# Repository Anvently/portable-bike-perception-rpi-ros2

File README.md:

# Cyclo-safe : a multi-sensor bike perception module (Camera, Dual 360° Lidar, GPS, Raspberry Pi, ROS2)

> The aim of the CycloSafe project is to improve cyclist safety by rigorously quantifying the risks they face, with a particular focus on those occurring when being overtaken by a motor vehicle.
> 
> To do this, we have equipped a bicycle with LIDARs (Light Detection and Ranging), a camera and a GNSS antenna.

This repository contains :
- the firmware intended to run on a **Raspberry Pi** to operate all the sensors and **take measurements**
- Various tools to **export**, **visualize**, and **analyze** the collected data
- Files required for **3D printing the case**
- File needed to manufacture the **dedicated PCB**.  
It was developed as part of an experimental data acquisition system for an academic research study on cyclist safety.

https://github.com/user-attachments/assets/d5b68dda-f3fe-4f50-86e3-c243446fb8e7

## Structure

> [**core/**](core/README.md): Directory intended to be installed on the Raspberry Pi. Contains:
> 	- ROS installation script
> 	- CycloSafe environment setup script
> 	- systemd services setup script
> 	- source code for the different ROS nodes

> [**design/**](design/README.md): Contains files related to the machining of the case and the dedicated PCB.

> [**scripts/**](scripts/README.md): Contains scripts useful for retrieving and exporting data.

> [**viewer/**](viewer/README.md): Directory intended to be installed on the host machine. Contains a set of tools for visualizing and analyzing the data.
> - [**ROS2.md**](viewer/ROS2.md): Documentation related to ROS2 and its use in the project.

> [**network.md**](network.md): Instructions for network configuration on both the host and the Raspberry Pi, enabling interaction between the two machines.

## About the Cyclo-safe project

This project is part of the broader **CycloSafe** research initiative conducted at the **Institut national de l’information géographique et forestière (IGN)**, which aims **to quantify the risks faced by cyclists when being overtaken by motor vehicles**.

This repository is dedicated **exclusively to the design and implementation of the acquisition module** used to collect measurement data for the study, along with a set of **tools for processing, visualizing, and analyzing** the recorded data.

It does **not** present or discuss the **results** of the study itself, and should not be directly associated with its conclusions or interpretations.

For more information on the full **CycloSafe** study, see:  
Emmanuel Cledat, Dirk Lauinger, Aymeric Dutremble, Maeve Blarel, Damien Louis Peller, Tristan Geslain, Alexandre Esteoulle, Elisabeth Giroux, Gabin Bourlon, Nicolas Pirard, Eric Ta — ***Cyclo-Safe: Quantitative study of the risks to which cyclists are exposed during their daily commute***.

## License

This project is licensed under the **CeCILL-B v1** license, a free software license fully compliant with French law, **based on the BSD 2-Clause license** and the principles of open source.

**Scope of the license** — The following materials are covered by the CeCILL-B license:
- Firmware code based on ROS2
- All project installation scripts and data analysis scripts
- Source code of data analysis tools, based on Qt and ROS2
- PCB design files
- 3D models and any corresponding f3d source files
- Assembly and user manuals for the module

You are **free to**:
- Use, modify, and redistribute this project under the terms of the CeCILL-B license
- Use this project for both **academic** and **commercial** purposes, without the strong copyleft constraints of GPL-like licenses
- Incorporate this code into proprietary software, as long as you respect the attribution requirements

You must:
- Include a copy of the CeCILL-B license with any redistributed version
- Retain notices of authorship and copyright
- Clearly indicate any modifications made

Author: [Nicolas Pirard (@Anvently)](https://github.com/Anvently)  
Contact: [pirard.nicolas@hotmail.fr](mailto:pirard.nicolas@hotmail.fr)  
Additional contributors: See [CONTRIBUTORS.md](./CONTRIBUTORS.md)

📄 Full license text: [CeCILL-B v1](http://www.cecill.info/licences/Licence_CeCILL-B_V1-en.html)  

📄 French version: [CeCILL-B v1](https://cecill.info/licences/Licence_CeCILL-B_V1-fr.html)  

---

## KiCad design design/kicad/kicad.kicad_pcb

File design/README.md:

# Cyclosafe design

Ce dossier contient les fichiers relatifs à la fabrication du boitier destiné à recevoir tous les composants ainsi que les fichiers de fabrication du PCB dédié.

- [Cyclosafe design](#cyclosafe-design)
- [Liste du matériel (BOM)](#liste-du-matériel-bom)
	- [COMPOSANTS](#composants)
	- [Quincaillerie](#quincaillerie)
	- [Inserts](#inserts)
	- [Total](#total)
- [Electronique](#electronique)
	- [Montage complet](#montage-complet)
	- [PCB dédié](#pcb-dédié)
		- [Fonctions](#fonctions)
		- [Schéma](#schéma)
		- [Aperçu](#aperçu)
- [Boitier imprimé en 3D](#boitier-imprimé-en-3d)
	- [Module waveshare UPS hat](#module-waveshare-ups-hat)
		- [Spécifications](#spécifications)
		- [Aperçu](#aperçu-1)
- [Fixation au vélo](#fixation-au-vélo)
- [Module de mesure amovible](#module-de-mesure-amovible)
	- [Partie haute](#partie-haute)
	- [Partie basse](#partie-basse)

---

https://github.com/user-attachments/assets/05b4201d-2b15-44bb-a8c5-ab20a0cb3d47

# Liste du matériel (BOM)

## COMPOSANTS

| Quantité | Nom de la pièce | Fonction | Masse (g) | Type | Origine | Coût estimé |
|----------|-----------------|----------|-----------|------|---------|-------------|
| 1 | Raspberry Pi 4 Model B | Firmware | 75.00 | PCB | Achat | 65.00 |
| 1 | UPS-HAT | Batterie | 120.00 | PCB | Achat | 22.00 |
| 1 | PCB custom | Électronique | 30.00 | PCB | Fabrication par un tiers | 8.75 |
| 1 | Raspberry Pi HQ Camera M12 mount | Capteur | 30.40 | Capteur | Achat | 52.00 |
| 1 | Objectif grand angle M12 | Capteur | 100 | Accessoire | Achat | 25.00 |
| 2 | Slamtec RPLiDAR C1 | Capteur | 110.00 | Capteur | Achat | 84.00 |
| 1 | Assemblage F | Fixation | 90.00 | Structure | Impression | 2.00 |
| 1 | Collier | Fixation | 37.00 | Structure | Impression | 0.5 |
| 1 | L76x GPS Module | Capteur | 5.00 | PCB | Achat | 15.00 |
| 1 | Boîtier bas | Structure | 130.00 | Structure | Impression | 1.89 |
| 1 | Boîtier haut | Structure | 101.00 | Structure | Impression | 2.23 |
| 1 | Carte SD | Firmware | 2.00 | Accessoire | Achat | 25.00 |
| 2 | Accu 18650 - 3400mAh | Batterie | 46.00 | Accessoire | Achat | 18.50 |
| 1 | Couvercle carte SD | Structure | 3.30 | Structure | Impression | 0.07 |
| 1 | Ficelle pour pin de verrouillage (diamètre < 2mm) | Fixation | 1.00 | Accessoire | Achat | 0.05 |
| 1 | Pin de verrouillage | Fixation | 1.65 | Structure | Impression | 0.05 |
| 1 | Câble molex picoblade 510210800 8-pin double-M 20cm | Connection gps-pcb | 2.00 | Accessoire | Achat | 0.50 |

## Quincaillerie

| Quantité | Nom de la pièce | Fonction | Masse (g) | Type | Origine | Coût estimé |
|----------|-----------------|----------|-----------|------|---------|--|
| 1 | Vis à tête hexagonale M2.5x6 | Trappe carte SD | 0.487 | Quincaillerie | Achat | 0.05
| 4 | Entretoise M/F M2.5x12 | Entretoise Raspberry | 1.999 | Quincaillerie | Achat | 0.50
| 4 | Entretoise M/F M2.5x18 | Entretoise HAT | 2.393 | Quincaillerie | Achat | 0.50
| 8 | Vis à tête hexagonale M2.5x12 | Lidars | 0.702 | Quincaillerie | Achat | 0.05
| 2 | Vis à tête hexagonale M2x8 | GPS | 0.341 | Quincaillerie | Achat | 0.05
| 3 | Vis à tête hexagonale M3x6 | Boîtiers | 0.796 | Quincaillerie | Achat | 0.05
| 8 | Vis à tête hexagonale M2.5x10 | UPS HAT & caméra | 0.630 | Quincaillerie | Achat | 0.05
| 1 | Vis à tête hexagonale M3x0.5x40 | Axe centrale du pin de blocage | 2.569 | Quincaillerie | Achat | 0.10
| 2 | Vis à tête hexagonale M4x0.7x40 | Collier | 4.776 | Quincaillerie | Achat | 0.10

## Inserts

| Quantité | Nom de la pièce | Fonction | Masse (g) | Type | Origine | Coût estimé
|----------|-----------------|----------|-----------|------|---------|--|
| 2 | Insert M4x8x6 | Collier | 2.00 | Quincaillerie | Achat | 0.08
| 1 | Insert M3x4x4.5 | Emboîtement supérieur | 1.00 | Quincaillerie | Achat | 0.05
| 2 | Insert M3x3x4.5 | Emboîtement latéral | 1.00 | Quincaillerie | Achat | 0.04
| 4 | Insert M2.5x4x3.5 | Raspberry | 1.00 | Quincaillerie | Achat | 0.04
| 2 | Insert M2x5x3.5 | GPS | 1.00 | Quincaillerie | Achat | 0.04
| 5 | Insert M2.5x5x3.5 | Couvercle SD + caméra | 1.00 | Quincaillerie | Achat | 0.04

## Total

| Quantité | Nom de la pièce | Fonction | Masse (g) | Type | Origine |Coût estimé
|----------|-----------------|----------|-----------|------|---------|--|
|Poids|||1102.25||
|Coût||||||431.17€

# Electronique

Le coeur du boitier comporte un assemblage de 3 circuits imprimés emboités les uns par desus les autres :
- un rapbeerry Pi 4B sur lequel vient se brancher la caméra
- un PCB personnalisé sur lequel vient se brancher les capteurs (2 LiDARS + un module GNSS)
- un module UPS (*Uninterruptible Power Supply*) alimentés par deux accus 18650 permettant de fournir le courant nécessaire (jusqu'à 3A), de protéger le circuit et de gérer la recharge

## Montage complet

## PCB dédié

 ### Fonctions
- permet de connecter les capteurs aux différentes interfaces UARTs du raspberry :
  - UART1 : LiDAR 1 (supérieur)
  - UART2 : LiDAR 2 (arrière)
  - UART5 : module GNSS
- intègre 3 LEDs pour avertir l'utilisateur des situations suivantes :
  - batterie faible (< 20 %) : voyant rouge allumé
  - carte sd pleine : voyant bleu allumé
  - démarrage/arrêt en cours : voyant jaune allumé sans clignotement
  - mesure en cours : voyant jaune clignotant
- intègre un bouton poussoir permettant de déclencher l'arrêt des mesures et d'éteindre en douceur le raspberry

### Schéma

### Aperçu

# Boitier imprimé en 3D

Le dossier [`kicad/`](kicad/) contient le projet Kicad 9.0 d'un PCB sur lequel viennent se brancher les différents capteurs et composants actifs (LEDs et bouton d'extinction).

Il prend la forme d'un hat pour raspberry et se connecte via le header de 40 pins.

## Module waveshare UPS hat

Il s'agit d'une alimentation non interruptible commercialisée par Waveshare.

### Spécifications

- alimenté par 2 accus 18650
- permet une utilisation constante du raspberry via batterie ou pendant la recharge sur secteur
- protection contre les court-circuits, polarité inversée, surcharge/décharge des batterie
- jusqu'à 2.5A en 5V
- monitoring de la tension des batteries (permettant de calculer le pourcentage restant) et de la consommation instantanée

### Aperçu

# Fixation au vélo

Cette partie là demeure sur la tige selle.

Un collier facilement déformable est placé autour de la tige selle et vient verrouiller l'assemblage femelle avec deux vis M4.

Le design du  collier est basé sur  par [**<ins>un modèle réalisé par Metamere</ins>**](https://www.printables.com/model/125810-bens-better-dropper-post-seat-bag-adapters-264-22-)  trouvé sur *printables.com* et distribué sous licence Creative Commons.

Il a été allongé, épaissi et simplifié par rapport au modèle original.

Le sytème de fixation est inspiré de celui du projet Open Source [**<ins>Open bike sensor</ins>**](https://github.com/openbikesensor/OpenBikeSensor3dPrintableCase), en particulier le système de glissière entre le support fixe demeurant sur la tige selle et le boitier principal.

# Module de mesure amovible

Il vient se glisseer dans l'assemblage femelle fixé sur la tige selle.

Le pin de verrouillage de la fixation s'insère dans un des trous prévus à cet effet et peut tourner sur lui-même afin de maintenir l'assemblage en place (un de chaque côté selon la place disponible sous ou au dessus du boitier).

Il se compose d'une partie basse et d'une partie haute qui viennent se clipser ensemble. 3 vis M3 permettent de verrouiller l'assemblage des deux boitiers.

## Partie haute

## Partie basse

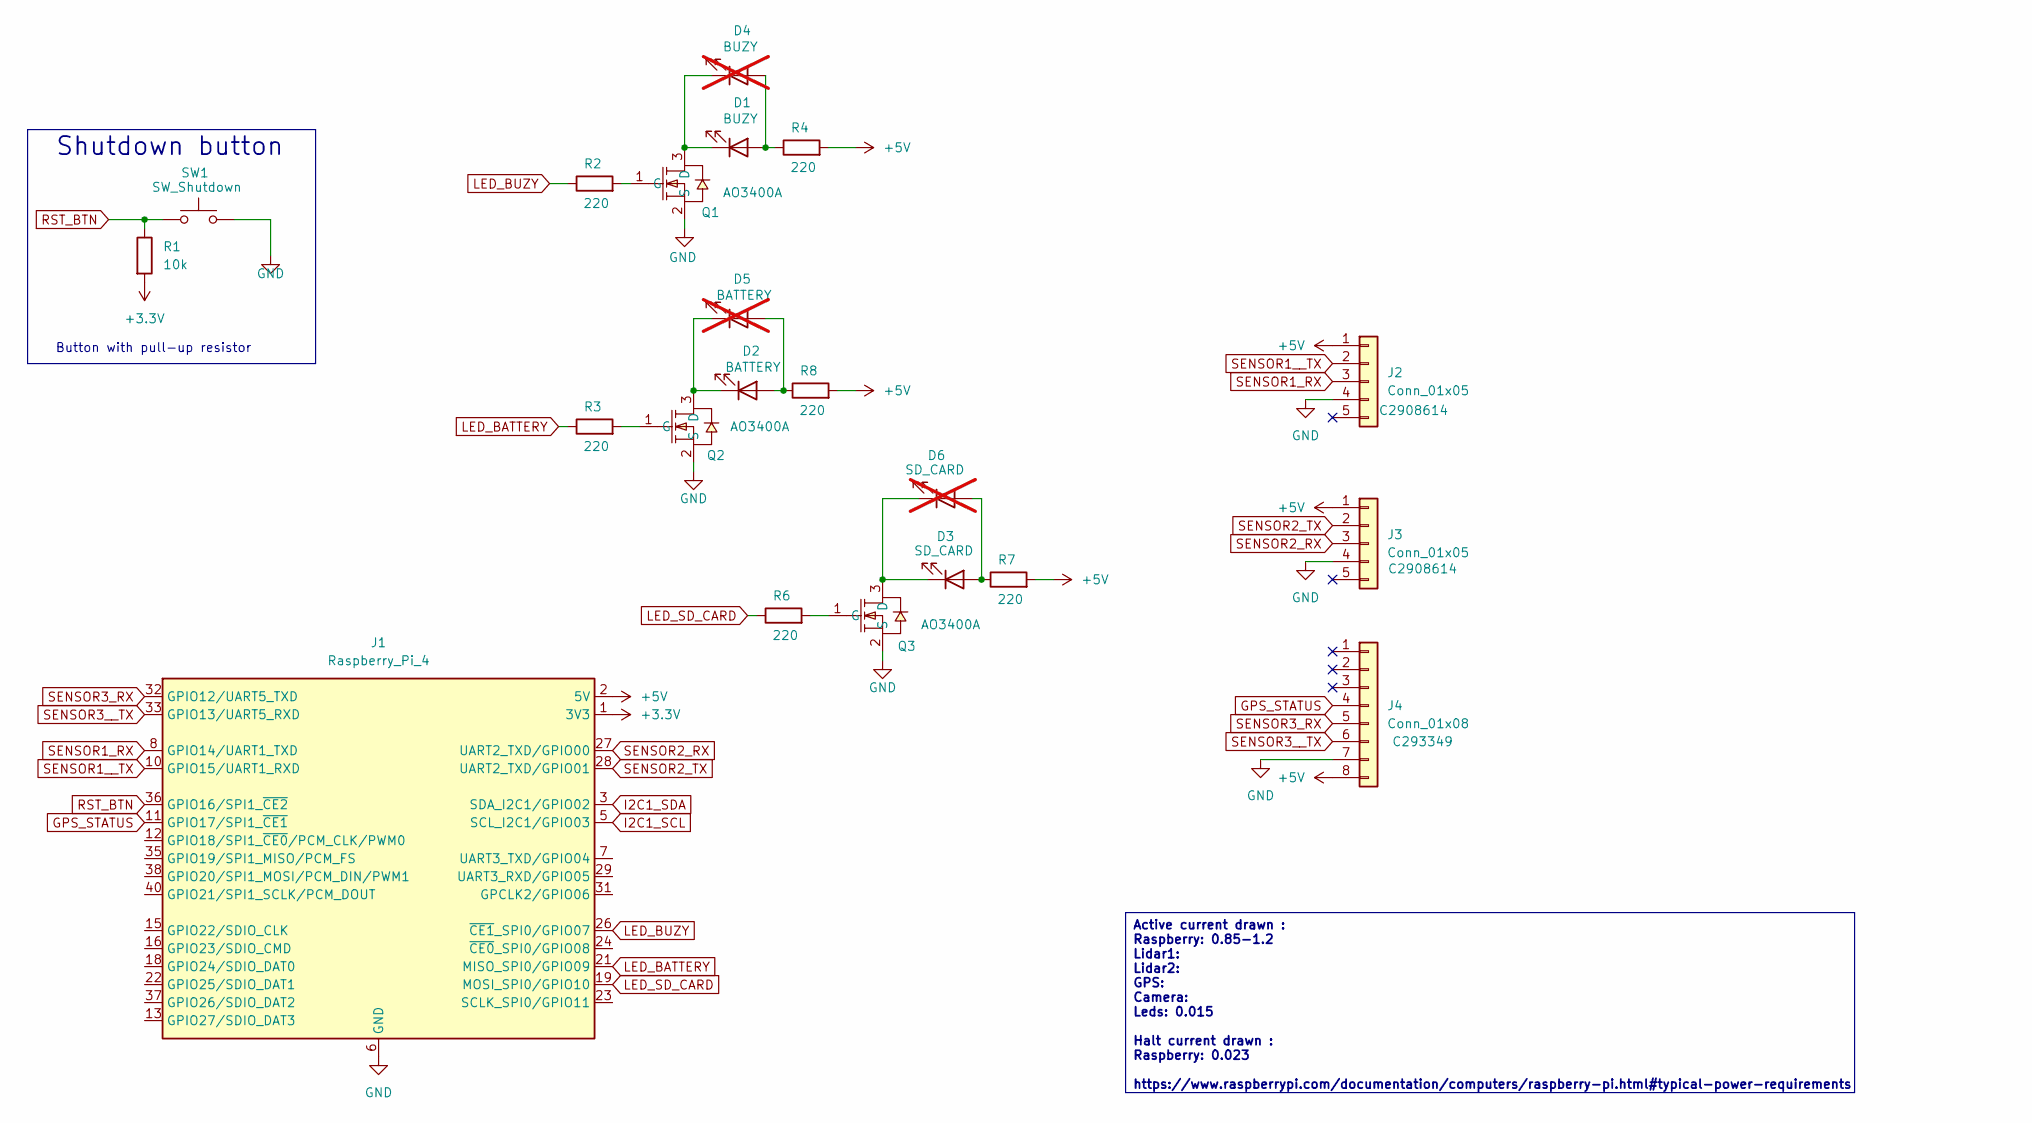
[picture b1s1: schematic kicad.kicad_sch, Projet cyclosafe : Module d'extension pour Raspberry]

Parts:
D1: BUZY; LED-SMD_L1.7-W0.6-RD-custom; LCSC Part C133119
D2: BATTERY; LED-SMD_L1.7-W0.6-RD-custom; LCSC Part C125114
D3: SD_CARD; LED-SMD_L1.7-W0.6-RD-custom; LCSC Part C125115
D4: BUZY; LED-TH_BD3.9-P2.54-FD; LCSC Part C133119; not fitted
D5: BATTERY; LED-TH_BD3.9-P2.54-FD; LCSC Part C125114; not fitted
D6: SD_CARD; LED-TH_BD3.9-P2.54-FD; LCSC Part C125115; not fitted
J1: Raspberry_Pi_4; HDR-TH_40P-P2.54-V-F-R2-C20-S2.54-2-reveresed; LCSC Part C35165
J2, J3: Conn_01x05; CONN-TH_WAFER-HA254WZ-5A; LCSC Part C2908614
J4: Conn_01x08; Molex_PicoBlade_53261-0871_1x08-1MP_P1.25mm_Horizontal; LCSC Part C293349
Q1, Q2, Q3: AO3400A; SOT-23-3_L2.9-W1.3-P1.90-LS2.4-BR; LCSC Part C20917
R1: 10k; R_0805_2012Metric; LCSC Part C17414
R2, R3, R4, R6, R7, R8: 220; R_0805_2012Metric; LCSC Part C17557
SW1: SW_Shutdown; SW-TH_TK-6580B-2; LCSC Part C2689830

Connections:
+3.3V: J1.1 (3V3), J1.17 (3V3), R1.2
+5V: J1.2 (5V), J1.4 (5V), J2.1, J3.1, J4.8, R4.2, R7.2, R8.2
GND: J1.6 (GND), J1.9 (GND), J1.14 (GND), J1.20 (GND), J1.25 (GND), J1.30 (GND), J1.34 (GND), J1.39 (GND), J2.4, J3.4, J4.7, Q1.2 (S), Q2.2 (S), Q3.2 (S), SW1.2
GPS_STATUS: J1.11 (GPIO17/SPI1_~CE1), J4.4
I2C1_SCL: J1.5 (SCL_I2C1/GPIO03)
I2C1_SDA: J1.3 (SDA_I2C1/GPIO02)
LED_BATTERY: J1.21 (MISO_SPI0/GPIO09), R3.1
LED_BUZY: J1.26 (~CE1_SPI0/GPIO07), R2.1
LED_SD_CARD: J1.19 (MOSI_SPI0/GPIO10), R6.1
unnamed: D1.2 (A), D4.2 (A), R4.1
unnamed: D1.1 (K), D4.1 (K), Q1.3 (D)
unnamed: D2.2 (A), D5.2 (A), R8.1
unnamed: D2.1 (K), D5.1 (K), Q2.3 (D)
unnamed: D3.2 (A), D6.2 (A), R7.1
unnamed: D3.1 (K), D6.1 (K), Q3.3 (D)
unnamed: Q1.1 (G), R2.2
unnamed: Q2.1 (G), R3.2
unnamed: Q3.1 (G), R6.2
RST_BTN: J1.36 (GPIO16/SPI1_~CE2), R1.1, SW1.1
SENSOR1_RX: J1.8 (GPIO14/UART1_TXD), J2.3
SENSOR1__TX: J1.10 (GPIO15/UART1_RXD), J2.2
SENSOR2_RX: J1.27 (UART2_TXD/GPIO00), J3.3
SENSOR2_TX: J1.28 (UART2_TXD/GPIO01), J3.2
SENSOR3_RX: J1.32 (GPIO12/UART5_TXD), J4.5
SENSOR3__TX: J1.33 (GPIO13/UART5_RXD), J4.6

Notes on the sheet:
Button with pull-up resistor
Shutdown button
Active current drawn : Raspberry: 0.85-1.2 Lidar1: Lidar2: GPS: Camera: Leds: 0.015 Halt current drawn : Raspberry: 0.023 https://www.raspberrypi.com/documentation/computers/raspberry-pi.html#typical-power-requirements

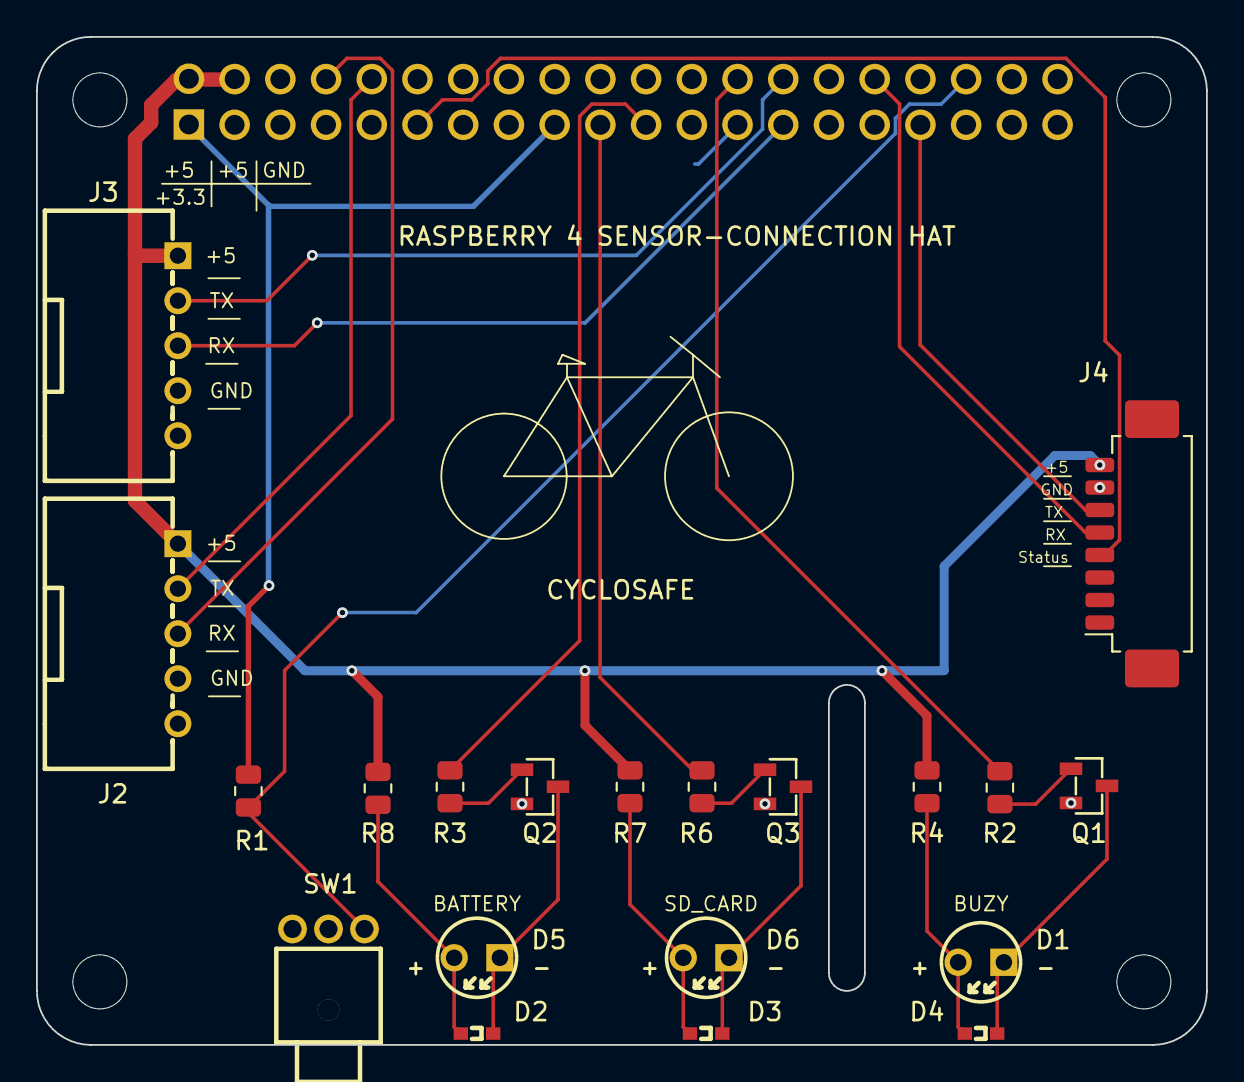
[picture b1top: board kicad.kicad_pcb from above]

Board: 2 copper layers, 65.0 x 56.0 mm, 21 parts (1 on the bottom side), 23 nets.

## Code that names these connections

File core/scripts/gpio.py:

#!/usr/bin/env python3
# -*- coding: utf-8 -*-
# Crerated on Tue Aug 05 2025
# Updated on Tue Aug 05 2025
#
# This file is part of Cyclosafe
# Copyright (c) 2025 Nicolas Pirard @Anvently
#
# This software is governed by the CeCILL license under French law and
# abiding by the rules of distribution of free software. You can use,
# modify and/or redistribute the software under the terms of the CeCILL
# license as circulated by CEA, CNRS and INRIA at:
# https://cecill.info/licences/Licence_CeCILL-B_V1-en.html

import os, time, sys, signal
import battery_monitor
import psutil
from battery_monitor import INA219
from gpiozero import Button, PWMLED

BTN_RST_GPIO = 16
LED_BATTERY_GPIO = 9
LED_BUZY_GPIO= 7
LED_SD_CARD_GPIO = 10

LED_BRIGHTNESS = float(os.getenv("LED_BRIGHTNESS", "1.0"))

button = Button(BTN_RST_GPIO, pull_up=True, bounce_time=0.1)

class BatteryException(Exception):
	pass

BUTTON_SHUTDOWN = 255
BATTERY_SHUTDOWN = 254

NBR_CELLS = 2
CHARGE_VOLTAGE = 4.2
MIN_VOLTAGE = 3

VOLTAGE_RANGE = CHARGE_VOLTAGE - MIN_VOLTAGE
BUS_CHARGE_VOLTAGE = NBR_CELLS * CHARGE_VOLTAGE
BATTERY_VOLTAGE_TRESHOLD = BUS_CHARGE_VOLTAGE - (NBR_CELLS * VOLTAGE_RANGE)

LOW_BATTERY_PERCENT = float(os.getenv("LOW_BATTERY_PERCENT", "0.2"))
LOW_BATTERY_TRESHOLD = BATTERY_VOLTAGE_TRESHOLD + (LOW_BATTERY_PERCENT * NBR_CELLS * VOLTAGE_RANGE)

LOW_STORAGE_TRESHOLD = int(os.getenv("LOW_STORAGE_TRESHOLD", "512"))

class GPIOController():
	def __init__(self):
		GPIOController.colors = [(255,0,0), (0,255,0), (0,0,255), (255,255,0), (0,255,255), (255,255,255)]
		self.color_index = 0
		self.gpio_state = {LED_BATTERY_GPIO: False, LED_BUZY_GPIO: False, LED_SD_CARD_GPIO: False}
		
		self.led_battery = PWMLED(LED_BATTERY_GPIO)
		self.led_busy = PWMLED(LED_BUZY_GPIO)
		self.led_sd = PWMLED(LED_SD_CARD_GPIO)
		
		for gpio in self.gpio_state:
			self.turn_off(gpio)
		self.pos = 0
		self.enable = True

		self.ina219 = INA219(1, addr=0x42)

	def turn_on(self, gpio):
		led = self._get_led(gpio)
		if led:
			led.value = LED_BRIGHTNESS
		self.gpio_state[gpio] = True

	def turn_off(self, gpio):
		led = self._get_led(gpio)
		if led:
			led.off()
		self.gpio_state[gpio] = False

	def _get_led(self, gpio):
		if gpio == LED_BATTERY_GPIO:
			return self.led_battery
		elif gpio == LED_BUZY_GPIO:
			return self.led_busy
		elif gpio == LED_SD_CARD_GPIO:
			return self.led_sd
		return None

	def toggle(self, gpio):
		if self.gpio_state[gpio]:
			self.turn_off(gpio)
		else:
			self.turn_on(gpio)

	def check_battery_state(self):
		if not self.ina219:
			return
		try:
			bus_voltage = self.ina219.get_bus_voltage_V()
		except:
			return
		if bus_voltage < BATTERY_VOLTAGE_TRESHOLD:
			raise BatteryException()
		elif bus_voltage < LOW_BATTERY_TRESHOLD:
			self.turn_on(LED_BATTERY_GPIO)

	def cleanup(self):
		self.turn_off(LED_BATTERY_GPIO)
		self.turn_off(LED_SD_CARD_GPIO)
		self.turn_on(LED_BUZY_GPIO)
		self.led_battery.close()
		self.led_sd.close()

	def routine(self, blink = True):
		shutdown_type = 0
		try:
			count = 0
			while not button.is_pressed:
				if count % 40 == 0:
					self.check_battery_state()
				if count % 120 == 0:
					self.check_sd_card()
				if blink:
					self.toggle(LED_BUZY_GPIO)
				time.sleep(0.25)
				count += 1
			print("Shutting down...")
			shutdown_type = BUTTON_SHUTDOWN
		except BatteryException:
			shutdown_type = BATTERY_SHUTDOWN
		
		self.cleanup()
		return shutdown_type

	def check_sd_card(self) -> bool:
		mb_available = psutil.disk_usage("/").free / 1024 / 1024
		print(mb_available, LOW_STORAGE_TRESHOLD)
		if (mb_available < LOW_STORAGE_TRESHOLD):
			self.turn_on(LED_SD_CARD_GPIO)
			return False
		self.turn_off(LED_SD_CARD_GPIO)
		return True

gpio_controler = GPIOController()

def signal_handler(signum, frame):
	gpio_controler.cleanup()
	sys.exit(0)

def main(args=None):
	global gpio_controler
	
	signal.signal(signal.SIGINT, signal_handler)
	signal.signal(signal.SIGTERM, signal_handler)
	shutdown_code = 0
	try:
		if gpio_controler.check_sd_card() == False:
			shutdown_code = gpio_controler.routine(blink=False)
		else:
			shutdown_code = gpio_controler.routine(blink=True)
	except:
		pass

	sys.exit(shutdown_code)

if __name__ == '__main__':
	main()

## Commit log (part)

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2025-03-10 inital commit, working on dockerfile
2025-03-10 fixed dockerfile
2025-03-10 dockerifle
2025-03-12 rm extra files
2025-03-12 sensor node
2025-03-12 added launch file with parameterized sensor node
2025-03-12 aded camera node (not tested)
2025-03-12 added camera_cv node
2025-03-13 camera node working - need to implement image queue
2025-03-13 new structure
2025-03-13 added save_files service
2025-03-13 tested save_files service
2025-03-13 fixed executable name
2025-03-14 added abstract serial sensor node and updated sensor example, added gps publisher base code
2025-03-17 gpio node
2025-03-17 test with gpio ok
2025-03-17 color palette
2025-03-17 wheel
2025-03-17 fixed wheel
2025-03-17 shutdown script
2025-03-17 changed gpio, added shutdown system
2025-03-18 gps node implemented
2025-03-18 fix exception handler for parsing serial node
2025-03-19 added cpp lidar node
2025-03-20 cpp lidar node: serial class implemented, some issue with line parsing and non printable character
2025-03-20 fixed lidar cpp
2025-03-20 eod - working on aggregator node
2025-03-21 hub - almost at the same point that python node - ready to compile
2025-03-21 fixed compil errors
2025-03-21 issue with future handling
2025-03-21 hub node: separate hpp/cpp files
2025-03-24 implemented ttldeque + outfile + suscriber_handler - ready to test
2025-03-24 hub timestamps fixed and working. TODO: Need the camera node to use ms timestamp synchronized with the hub. Need something else (forgot)
2025-03-25 global time implemented and working. TODO: implement ros time in ASerialSensor
2025-03-26 launch config implemented: custom log_level/log folder/ all node share the same start_time and use ros time
2025-03-26 implemented ros bag in launch description
2025-03-26 fixing to cpp 17
2025-03-26 c++ 17 compiled
2025-03-26 now using compressed image msg
2025-03-26 fioxed
2025-03-26 added rp_lidar to launch config
2025-03-26 debugging picamera
2025-03-27 *range_circle*
2025-03-27 viewer launch configuration ok
2025-03-27 added scan file output
2025-03-27 changed gpio routine
2025-03-28 small fix
2025-03-28 enabled compression on launch
2025-03-28 added port name resolution + changed camera frquency
2025-03-28 fixed
2025-03-28 preview fixed
2025-03-28 optimize camera node
2025-03-28 fixed camera
2025-03-28 changed image view in view launch config
2025-03-28 added doubloon directory security, but will never happen
2025-04-01 implementing gps interface and improving gps informations
2025-04-03 4 sonar config + rplidar on uart
2025-04-03 tag update sonar
2025-04-03 removed camera preview
2025-04-03 camera adjust
2025-04-04 updated sonar visualizations
2025-04-04 gpio node now systemd with clean shutdown
2025-04-04 update log dir creation
2025-04-04 change executable permission for script
2025-04-04 fixing systemd service
2025-04-04 update sonar frequency
2025-04-04 fixed camera colors
2025-04-06 added bag player
2025-04-08 added graph features on player
2025-04-09 debugging sonar error flow
2025-04-09 added sonar5
2025-04-09 debugging sonar
2025-04-09 fixed sonar debug
2025-04-10 re-enabled bag compression
2025-04-10 ézfzefze
2025-04-11 implemented Marker/MarkerCategory and Peakdection for player
2025-04-11 implemented depassement/croisement custom form, highlight current peaks
2025-04-11 markers is now a dictionnary to avoid doubloons for the same stamp - implemented auto import at startup
2025-04-11 starting to implement csv export/import/meerge
2025-04-14 few fix
2025-04-14 eod, few fixes and improveements for csv import/export
2025-04-15 csv format edit + fix on marker enum values
2025-04-16 modif launch config to work with 2 rs232 sonars
2025-04-16 added unit parameter for serial sensor, added sonar_rs232 node
2025-04-17 added time update script
2025-04-17 implemented sonar_sr04 node removed the ability to update parameter after the node start for ASerialSensor (too much issue with CPU load and seems useless)
2025-04-17 fix setup.py
2025-04-18 rm useless files and added COLCON_IGNORE to cyclosafe_lidar
2025-04-22 - player: updated bag basedir resolution for compressed bag (instead of tmp folder) - player: always ask category when adding a new marker
2025-04-23 - added node to use LV10X0 sonar with pulse width
2025-04-23 - added ldlidar node submodule - removed sonar from launch config - redone package structure - added ldlidar launch description into cyclosafe.launch.py
2025-04-24 gps parsing updated to be more resilient with other service - fixed active sat counting - TODO: gps L80-m39 sometime raises serial exception repetively
2025-04-24 added battery monitor script + killswitch in gpio script
2025-04-24 Cyclosafe lidar cpp package: - implemented new methods on Serial - implemented abstract driver class for all 3 benewake lidar
2025-04-25 cyclosafe lidar node and driver done and compiled without warning. Not tested
2025-04-25 deleted ldlidar submodule for stl-19 (it was the wrong reference
2025-04-25 added ldlidar stl27l submodule + added node to launch config
2025-04-25 added ldlidar stl27l submodule + added node to launch config + added rplidar to launch config (2x360° lidar)
2025-04-25 added tof_lidar python node
2025-04-29 removed format
2025-04-29 ldlidar is now a forked repo fixed pull up config for button
2025-04-30 fixing gpio issue
2025-04-30 debugging tof lidar
2025-04-30 - refacto both launch files including a central config module - fixed lidar undefined frame_id - tof lidar working - sonar_lv_pw very instable - WORKING ON: tf-mini-plus, not working: some issues wit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
2025-05-05 driver not working yet, some issue with serial configuration
2025-05-06 - added benewake lidars to launch config - expanded port resolution to node parameter (matching any 'port' or 'serial_port' parameter)
2025-05-06 both benewake lidar share the same config rplidar is now vertical at the back
2025-05-06 adding delay to launch config
2025-05-06 fixed nreceive_peek issue when serial is reading to fast (read of single byte). find_sequence function is now able to dectect non-contiguous sequence (sequence overlapping multiple read)
2025-05-07 - lidar node are now locking serial port for themselves
2025-05-07 enable file splitting on bag record re-enabled camera node
2025-05-12 - added python script to import bag via scp and decompress + convert them into single bag - fixed tof_lidar + benewake_lidar : invalid strength result as a published nan - range_circle_transform : de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
2025-05-13 added tof_camera submodule
2025-05-14 updated ref commit for arducam_tof_camera
2025-05-14 testing ups
2025-05-14 enabled stl27 lidar
2025-05-15 - viewer launch configuration now use urdf model (with 3d models) to transform everything to world frame - battery monitor script updated to use a different ina219 library - added rviz_satellite plug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
2025-05-16 import_recordings.py: implemented bag reparation, gps_exporter.py: script to export gps topic to gpx trace
2025-05-19 need to test core installation scripts
2025-05-19 lots of readme added
2025-05-19 writing cyclosafe readme node
2025-05-20 few fixes and readme improved
2025-05-20 few fixes in obsolete nodes + added config argument to cyclosafe.launch.py + more to readme
2025-05-20 made battery_monitor script executable
2025-05-21 edited launch config.py
2025-05-21 fixed readme missing .md extension
2025-05-21 core+scripts documentation finished, added network documentation
2025-05-21 moved viewer packages to viewer/src
2025-05-21 Config.py classes are now part of a dedicated pacakge, this package is referenced in viewer via a symlink
2025-05-21 missing link in readme
2025-05-21 eod: starting to work on viewer README, ros introduction needs to be moved elsewhere
2025-05-22 added cyclosafe_viewer readme
2025-05-22 wip : cyclsoafe_player
2025-05-23 documntation for viewer part donee - moved resources to dedicated folder in each package
2025-05-23 Testing video preview
2025-05-23 docu done
2025-05-23 video preview
2025-05-23 rm video file, video is now a user attachment
2025-06-20 Update .bashrc
    Fixed alias definition in .bashrc when ROS Jazzy is not installed ("echo" command was missing)
2025-06-30 prod update
2025-06-30 added missing step files
2025-06-30 rm unused src for prod firmware - readme updated
2025-06-30 forgot readme files in last commit
2025-06-30 cleaning non-used nodes and packages, implemented some CONSTANT variables for gpio.py as env variables + added disk storage monitoring
2025-06-30 edited library path for kicad symbol
2025-06-30 added design folder in prod branch
2025-07-02 added design files
2025-07-02 changed pourcent with percent + updated bashrc for core + updated sd card check in gpio.py
2025-07-02 added bom file
2025-07-02 added resume-electronique
2025-07-02 missing legend on drawing
2025-07-02 Create LICENSE
2025-07-02 ajout de visuels
2025-07-02 ajout de visuels pour le boitier coupe en deux
2025-07-08 fixed ip_config script
2025-07-08 fixing setup_service script
2025-07-09 updated launch config
2025-07-16 - changed camera config to consume less storage - fix on scripts - doc updated
2025-07-17 added launch wrapper for cyclosafed monitoring updated systemd services to be more robust added date verification in gps_time.sh centralized logging file for gpio.sh and launch_wrapper.sh
2025-07-18 fixing issue with env variable in viewer .bashrc script
2025-07-18 changing username
2025-08-04 fixed gps_time script (month were treated as octal numbers), updated LICENCE and added NOTICE + licence section in readme, add manuel, readded gpx_exporter.py, removed extra files, commented independ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
2025-08-05 changed licence to GPL (Ccil) and added header in source code
2025-08-05 added feature in cyclosafe_player to visualize lidar data as curve, sampling range of points defined with min_angle and max_angle
2025-08-05 rm TODO
2025-08-05 added instruction in sd_card flash readme for how to set custom parameter
2025-08-05 - version 1.0.1 (associated with firmware.img.xz)
2025-08-07 cyclosafe_player: visualize gps trace on map widget + live position + added gps data curve and live output
2025-08-07 updated cyclosafe_player image preview, changed shutdown button max latency from 0.5s to 0.25s
2025-08-08 added env check in import_recording script, added python3-rich in ROS env, updated README
2025-08-08 fixed missing dependancy in cyclosafe_player
2025-08-11 added ROS2.md reference in core/README.md
2025-08-11 fix in cyclosafe_player with nan
2025-08-11 ajout des 3 fichiers script csv converter + contributions added
2025-08-11 missing script fikle
2025-08-13 missing import in gpio.py
2025-08-13 Updated version for csv extraction
2025-08-13 merged code with eric
2025-08-13 VERSION 1.1
2025-08-13 Correct version of compressed_images_extraction.py
2025-08-14 cyclosfae viewer env install instructions: fix command to add source to any terminal + improved ambiguous recommendation
2025-08-14 last commit had an error
2025-08-14 added schematic, implemented invert_lidar argument
2025-08-15 added index.html redirecting to github repo (for google indexation)
2025-08-15 increased refresh delay
2025-08-15 5s delay
2025-08-15 rm index.html
2025-08-19 encryption base setup
2025-08-20 encryption base setup replaced all csv_conversion with single bag_converter.py
2025-08-21 fix: observer thread join not blocking anymore, number of expected node is checked twice, fix warning command to check if module is shutdown while cyclosafed.service still active
2025-08-21 readme and diagrams updated to documente encryption
2025-08-21 reduced delay for encryptor stability from 3 to 2s, and increased systemd stop timeout from 10s to 13s
2025-08-21 debugging encryptor 5s latency when compressing last file
2025-08-22 VERSION 1.2 encryptor: process_final_files now check for metadata.yaml existence instead of checking file stability gpio.py : use gpiozero instead of pigpio removed pigpiod service
2025-08-22 fixed encrypt option error in launch_wrapper.sh, updated readme for new env variables, added EXPECTED_NODE ENV variable
2025-08-22 added no_compression parameter for camera node
2025-08-28 updated scripts/README with bag_converter and decryptor
